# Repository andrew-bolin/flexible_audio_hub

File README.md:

# flexible_audio_hub

## The Challenge

My ears and speakers will last a lifetime (I hope), but home theatre audio standards do not. My old stereo amplifier works fine, why can't I get an HDMI upgrade module that gives it CEC (control via TV remote). If I buy a 5.1 channel amplifier, why do I have to throw it in the bin to upgrade to Atmos?

A modern AVR (Audio-Video Receiver) is a fantastic piece of technology, but they are available only in certain fixed configurations and are not easily modifiable.

## How Will We Alleviate The Problem?

1. A modular "hub" that allows incremental upgrades, e.g. an extra analog input, an extra two channels of amplification, or even another hub...
2. Compatibility with other open source projects in this field.
3. Ability to make use of readily available (cheap!) modules from China.
4. Ability to connect to home automation systems (e.g. limit the volume and turn off the subwoofer if someone's in bed, or play your wake-up alarm at rock concert levels throughout the house)

The modular system will be entirely open-source so that any interested person can make their own module to serve their unique needs (or for fun). Eventually I would like to see compatible modules available from multiple vendors (much like Raspberry Pi & Arduino add-ons).

## (Notes Working Towards) The Specification

[The Current Specification](SPECIFICATION.md) - very much a work in progress!

The first stage will be electrical & communications protocol only.

Currently, I am deciding on a connector - if anyone knows a connector that is a reasonable pitch (0.5 - 2.5mm), keyed, upwards-compatible with extra pins (e.g. a 16-pin plug can fit into a 20-pin socket), and **cheap**, please get in contact!

*Previously, I started a similar project using a backplane, because edge connectors are cheap, but the design I was using had the switching complexity by necessity in every module, was difficult to integrate into a chassis, and did not offer full flexibility for multiple simultaneous outputs. Now I will move that complexity to a "hub" board.*

Each module should (yes, it's optional) have an ID EEPROM & accept a few basic commands (Enable, select channel) via I2C. This can be achieved via a PCA9500 I/O expander or ATtiny, for example. Modules without the ID/Control interface will require more configuration effort and might waste a bit more power (the central hub will probably not have power switches per module).

The hub will be controlled by I2C, and a C++ library will be provided that will be usable via Arduino and Raspberry Pi. The hub will be able to be daisy-chained. 

----

These files are distributed under The TAPR Open Hardware License, version 1.0.  
See LICENSE.txt or https://www.tapr.org/ohl.html

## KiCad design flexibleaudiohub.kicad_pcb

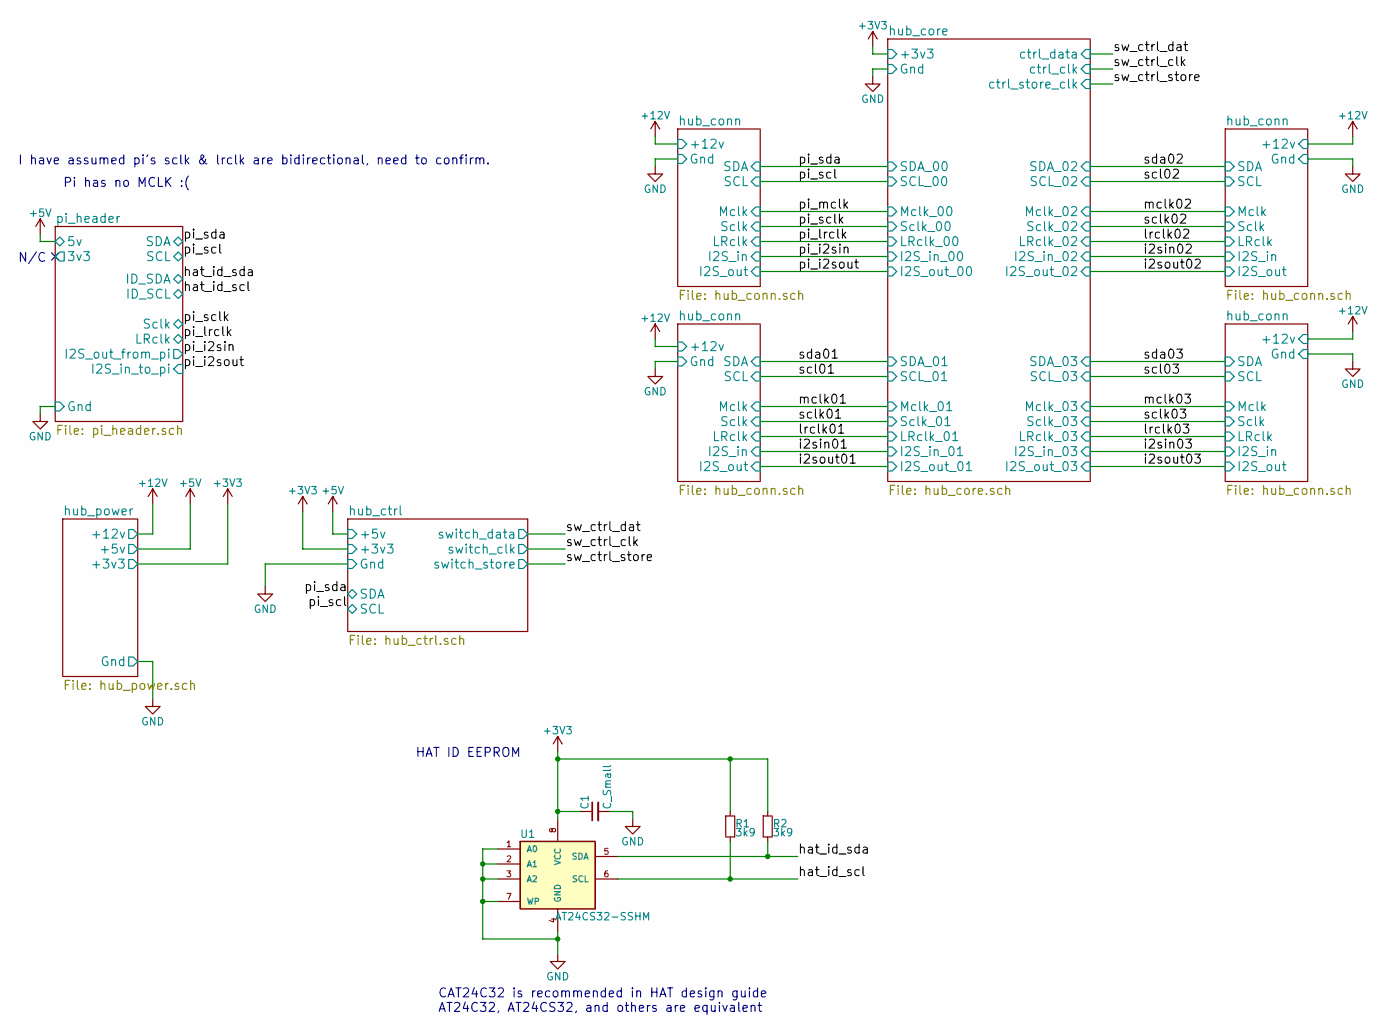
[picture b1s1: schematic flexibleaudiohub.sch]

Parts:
C1: C_Small; C_0805_HandSoldering
R1, R2: 3k9; R_0805_HandSoldering
U1: AT24CS32-SSHM; SOIC-8_3.9x4.9mm_Pitch1.27mm

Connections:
+3V3: C1.1, R1.1, R2.1, U1.8 (VCC); also elsewhere on the board
/hat_id_scl: R1.2, U1.6 (SCL); also elsewhere on the board
/hat_id_sda: R2.2, U1.5 (SDA); also elsewhere on the board
GND: C1.2, U1.1 (A0), U1.2 (A1), U1.3 (A2), U1.4 (GND), U1.7 (WP); also elsewhere on the board

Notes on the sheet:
N/C
Pi has no MCLK :(
I have assumed pi's sclk & lrclk are bidirectional, need to confirm.
HAT ID EEPROM
CAT24C32 is recommended in HAT design guide AT24C32, AT24CS32, and others are equivalent

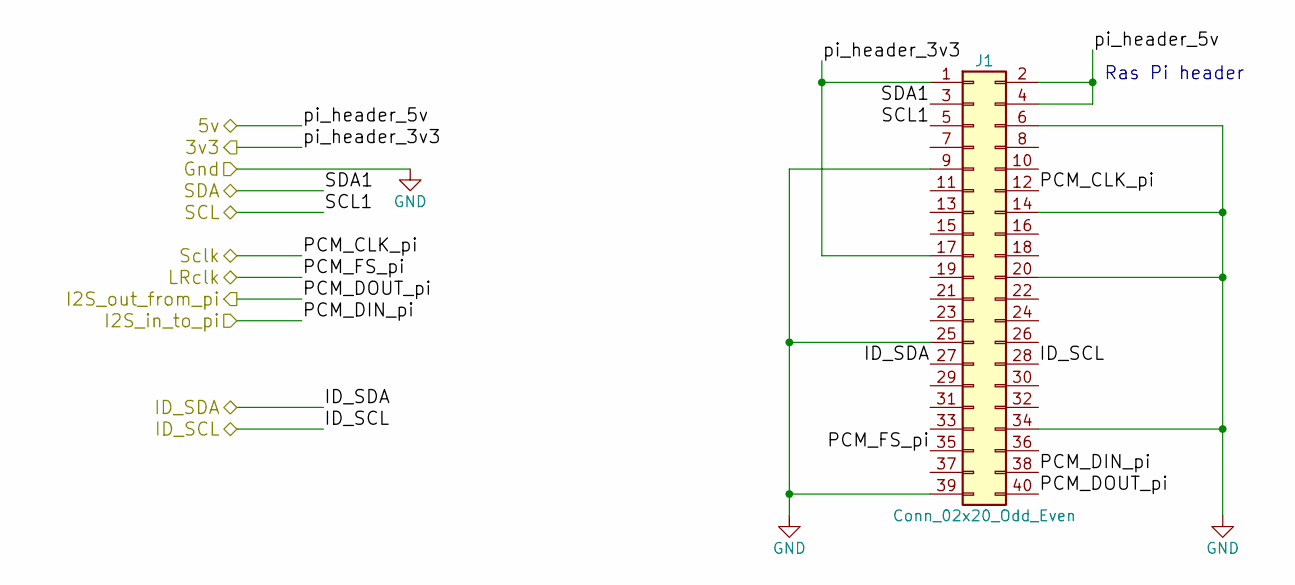
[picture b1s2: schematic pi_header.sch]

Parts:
J1: Conn_02x20_Odd_Even; Pin_Header_Straight_2x20_Pitch2.54mm

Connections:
+5V: J1.2, J1.4; also elsewhere on the board
/hat_id_scl: J1.28; also elsewhere on the board
/hat_id_sda: J1.27; also elsewhere on the board
/pi_header/3v3: J1.1, J1.17
/pi_i2sin: J1.40; also elsewhere on the board
/pi_i2sout: J1.38; also elsewhere on the board
/pi_lrclk: J1.35; also elsewhere on the board
/pi_scl: J1.5; also elsewhere on the board
/pi_sclk: J1.12; also elsewhere on the board
/pi_sda: J1.3; also elsewhere on the board
GND: J1.6, J1.9, J1.14, J1.20, J1.25, J1.34, J1.39; also elsewhere on the board

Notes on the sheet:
Ras Pi header

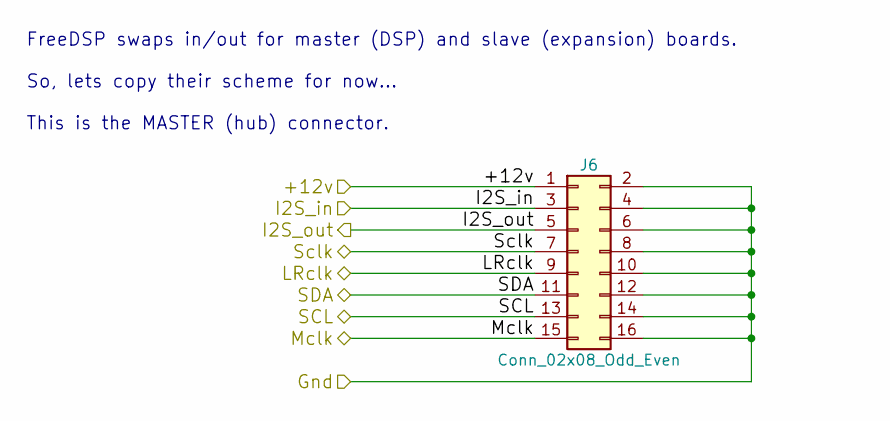
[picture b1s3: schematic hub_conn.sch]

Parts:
J2: Conn_02x08_Odd_Even; Pin_Header_Straight_2x08_Pitch2.54mm

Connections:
+12V: J2.1; also elsewhere on the board
/i2sin03: J2.3; also elsewhere on the board
/i2sout03: J2.5; also elsewhere on the board
/lrclk03: J2.9; also elsewhere on the board
/mclk03: J2.15; also elsewhere on the board
/scl03: J2.13; also elsewhere on the board
/sclk03: J2.7; also elsewhere on the board
/sda03: J2.11; also elsewhere on the board
GND: J2.2, J2.4, J2.6, J2.8, J2.10, J2.12, J2.14, J2.16; also elsewhere on the board

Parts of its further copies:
J4, J5, J6: Conn_02x08_Odd_Even; Pin_Header_Straight_2x08_Pitch2.54mm

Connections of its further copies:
+12V: J4.1, J5.1, J6.1; also elsewhere on the board
/i2sin01: J5.3; also elsewhere on the board
/i2sin02: J4.3; also elsewhere on the board
/i2sout01: J5.5; also elsewhere on the board
/i2sout02: J4.5; also elsewhere on the board
/lrclk01: J5.9; also elsewhere on the board
/lrclk02: J4.9; also elsewhere on the board
/mclk01: J5.15; also elsewhere on the board
/mclk02: J4.15; also elsewhere on the board
/pi_i2sin: J6.3; also elsewhere on the board
/pi_i2sout: J6.5; also elsewhere on the board
/pi_lrclk: J6.9; also elsewhere on the board
/pi_mclk: J6.15; also elsewhere on the board
/pi_scl: J6.13; also elsewhere on the board
/pi_sclk: J6.7; also elsewhere on the board
/pi_sda: J6.11; also elsewhere on the board
/scl01: J5.13; also elsewhere on the board
/scl02: J4.13; also elsewhere on the board
/sclk01: J5.7; also elsewhere on the board
/sclk02: J4.7; also elsewhere on the board
/sda01: J5.11; also elsewhere on the board
/sda02: J4.11; also elsewhere on the board
GND: J4.2, J4.4, J4.6, J4.8, J4.10, J4.12, J4.14, J4.16, J5.2, J5.4, J5.6, J5.8, J5.10, J5.12, J5.14, J5.16, J6.2, J6.4, J6.6, J6.8, J6.10, J6.12, J6.14, J6.16; also elsewhere on the board

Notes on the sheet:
FreeDSP swaps in/out for master (DSP) and slave (expansion) boards. So, lets copy their scheme for now... This is the MASTER (hub) connector.

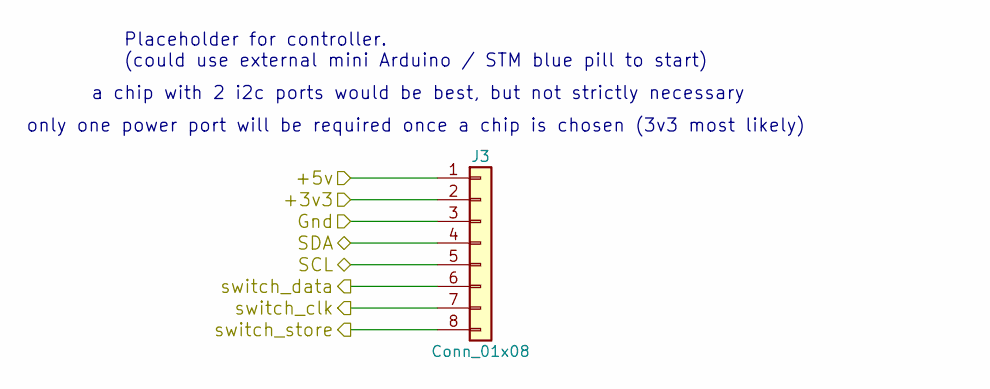
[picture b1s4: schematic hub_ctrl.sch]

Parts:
J3: Conn_01x08; Pin_Header_Straight_1x08_Pitch2.54mm

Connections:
+3V3: J3.2; also elsewhere on the board
+5V: J3.1; also elsewhere on the board
/pi_scl: J3.5; also elsewhere on the board
/pi_sda: J3.4; also elsewhere on the board
/sw_ctrl_clk: J3.7; also elsewhere on the board
/sw_ctrl_dat: J3.6; also elsewhere on the board
/sw_ctrl_store: J3.8; also elsewhere on the board
GND: J3.3; also elsewhere on the board

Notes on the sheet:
Placeholder for controller. (could use external mini Arduino / STM blue pill to start)
a chip with 2 i2c ports would be best, but not strictly necessary
only one power port will be required once a chip is chosen (3v3 most likely)

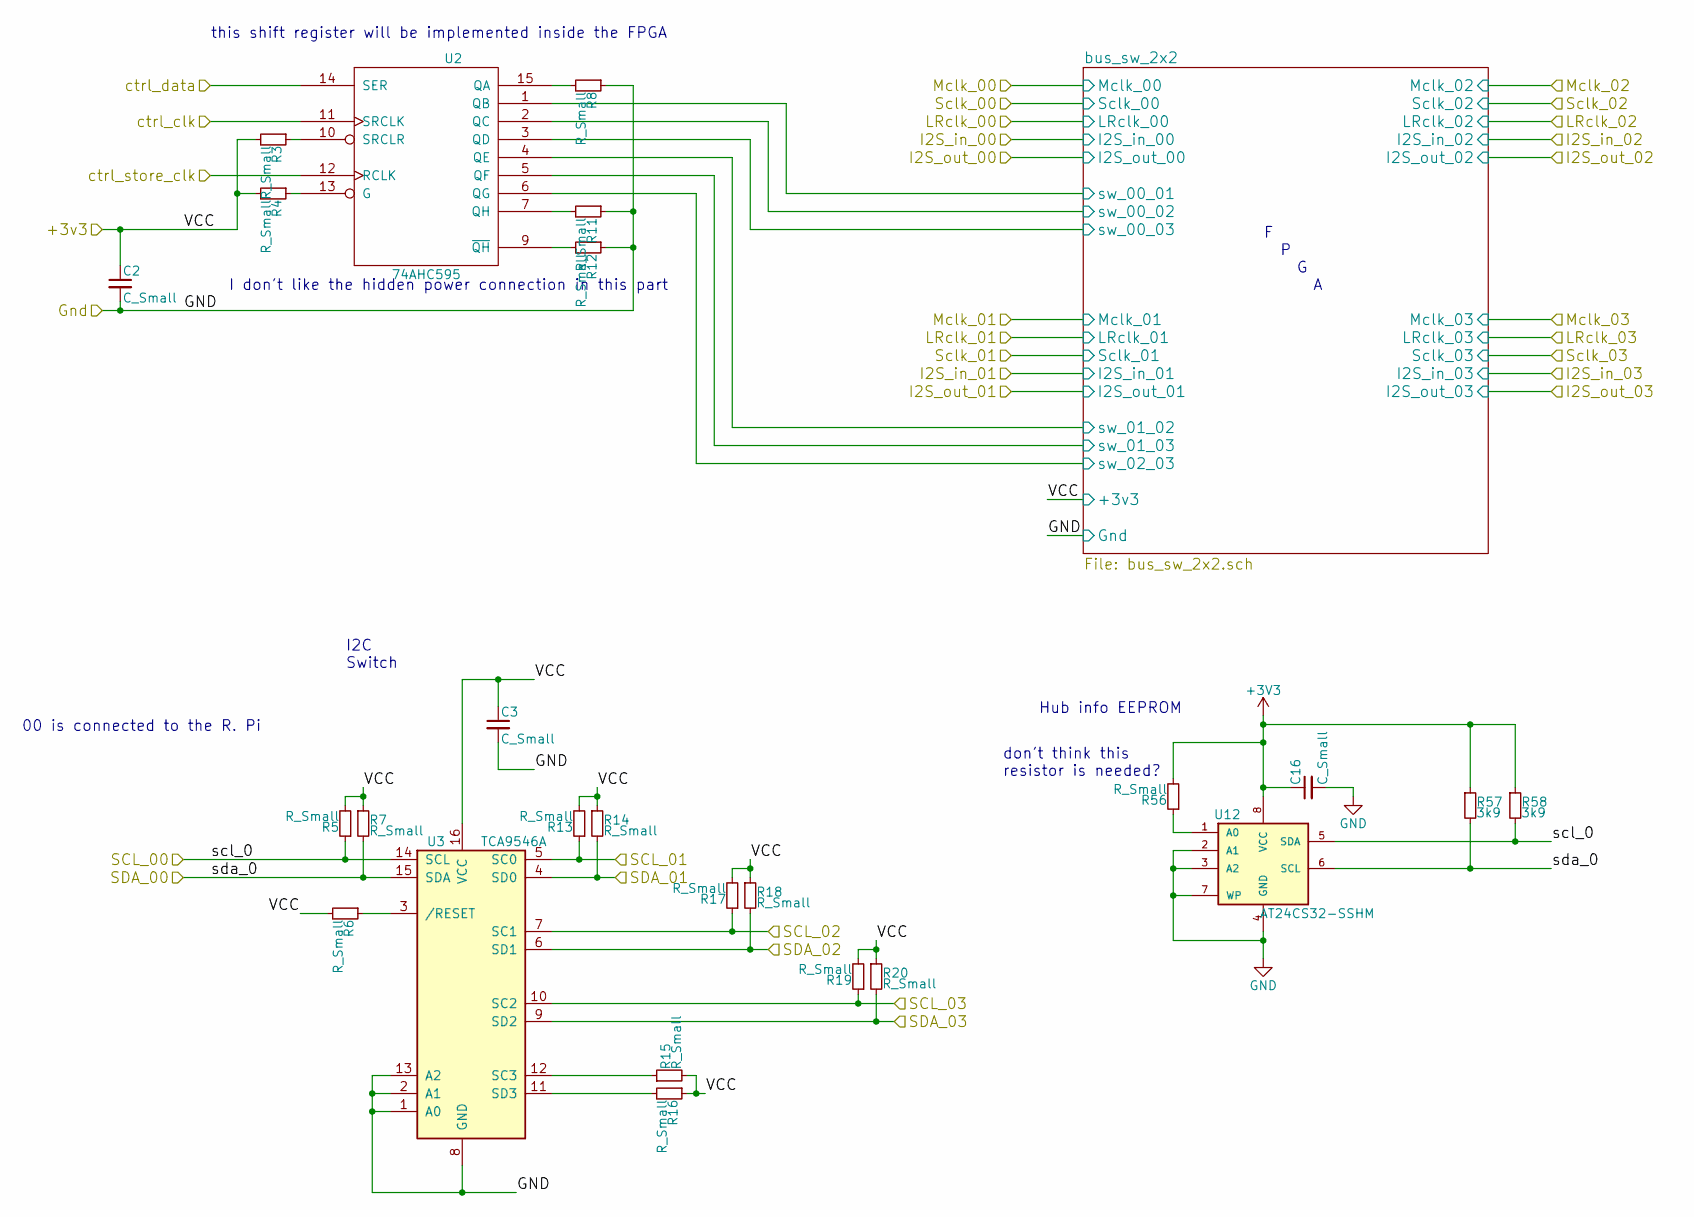
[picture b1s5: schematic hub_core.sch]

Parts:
C2, C3, C16: C_Small; C_0805_HandSoldering
R3, R4, R5, R6, R7, R8, R11, R12, R13, R14, R15, R16, R17, R18, R19, R20, R56: R_Small; R_0805_HandSoldering
R57, R58: 3k9; R_0805_HandSoldering
U2: 74AHC595; SOIC-16_3.9x9.9mm_Pitch1.27mm
U3: TCA9546A; TSSOP-16_4.4x5mm_Pitch0.65mm
U12: AT24CS32-SSHM; SOIC-8_3.9x4.9mm_Pitch1.27mm

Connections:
+3V3: C2.1, C3.1, C16.1, R3.2, R4.2, R5.2, R6.2, R7.1, R13.2, R14.1, R15.2, R16.1, R17.2, R18.1, R19.2, R20.1, R56.2, R57.1, R58.1, U2.16 (VCC), U3.16 (VCC), U12.8 (VCC); also elsewhere on the board
/hub_core/bus_sw_2x2/sw_00_01: U2.1 (QB); also elsewhere on the board
/hub_core/bus_sw_2x2/sw_00_02: U2.2 (QC); also elsewhere on the board
/hub_core/bus_sw_2x2/sw_00_03: U2.3 (QD); also elsewhere on the board
/hub_core/bus_sw_2x2/sw_01_02: U2.4 (QE); also elsewhere on the board
/hub_core/bus_sw_2x2/sw_01_03: U2.5 (QF); also elsewhere on the board
/hub_core/bus_sw_2x2/sw_02_03: U2.6 (QG); also elsewhere on the board
/pi_scl: R5.1, R58.2, U3.14 (SCL), U12.5 (SDA); also elsewhere on the board
/pi_sda: R7.2, R57.2, U3.15 (SDA), U12.6 (SCL); also elsewhere on the board
/scl01: R13.1, U3.5 (SC0); also elsewhere on the board
/scl02: R17.1, U3.7 (SC1); also elsewhere on the board
/scl03: R19.1, U3.10 (SC2); also elsewhere on the board
/sda01: R14.2, U3.4 (SD0); also elsewhere on the board
/sda02: R18.2, U3.6 (SD1); also elsewhere on the board
/sda03: R20.2, U3.9 (SD2); also elsewhere on the board
/sw_ctrl_clk: U2.11 (SRCLK); also elsewhere on the board
/sw_ctrl_dat: U2.14 (SER); also elsewhere on the board
/sw_ctrl_store: U2.12 (RCLK); also elsewhere on the board
GND: C2.2, C3.2, C16.2, R8.1, R11.1, R12.1, U2.8 (GND), U3.1 (A0), U3.2 (A1), U3.8 (GND), U3.13 (A2), U12.2 (A1), U12.3 (A2), U12.4 (GND), U12.7 (WP); also elsewhere on the board
unnamed: R3.1, U2.10 (SRCLR)
unnamed: R4.1, U2.13 (G)
unnamed: R6.1, U3.3 (/RESET)
unnamed: R8.2, U2.15 (QA)
unnamed: R11.2, U2.7 (QH)
unnamed: R12.2, U2.9 (~QH)
unnamed: R15.1, U3.12 (SC3)
unnamed: R16.2, U3.11 (SD3)
unnamed: R56.1, U12.1 (A0)

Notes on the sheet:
I2C Switch
00 is connected to the R. Pi
F P G A
this shift register will be implemented inside the FPGA
I don't like the hidden power connection in this part
Hub info EEPROM
don't think this resistor is needed?

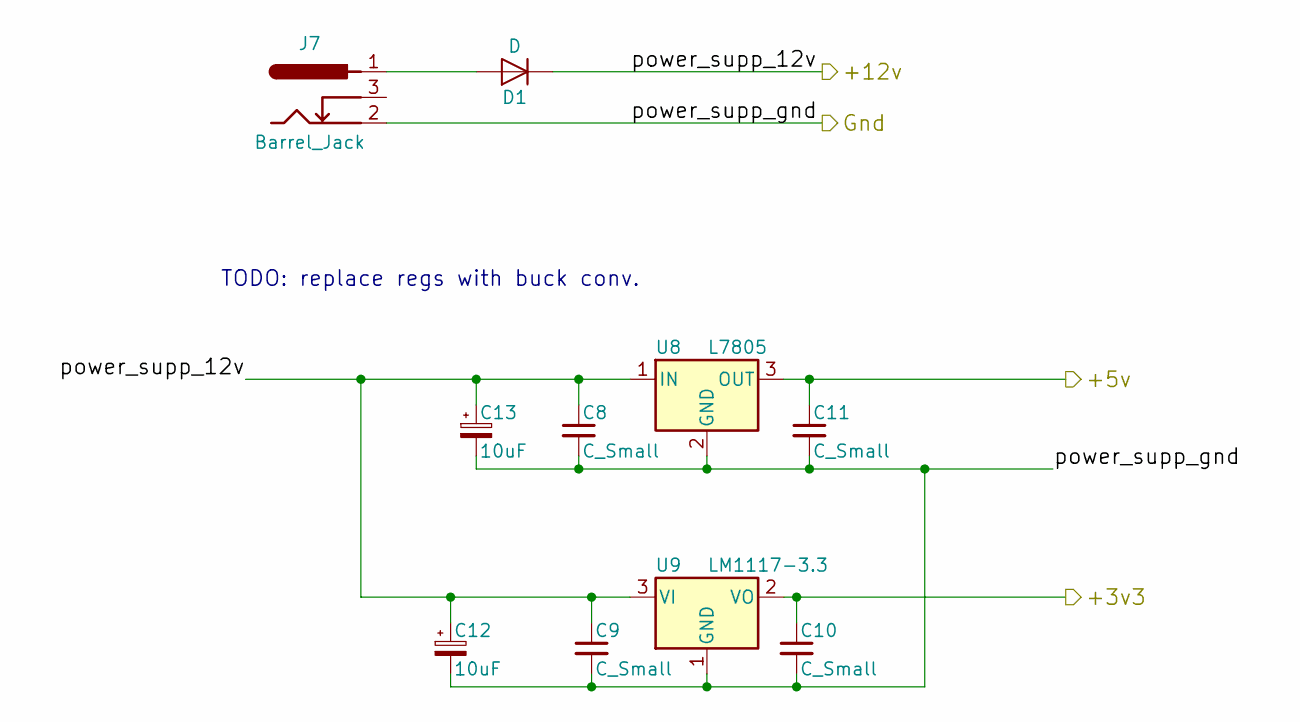
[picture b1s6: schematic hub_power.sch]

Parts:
C8, C9, C10, C11: C_Small; C_0805_HandSoldering
C12, C13: 10uF; CP_Radial_D5.0mm_P2.00mm
D1: D; D_5W_P10.16mm_Horizontal
J7: Barrel_Jack; BARREL_JACK
U8: L7805; TO-220_Vertical
U9: LM1117-3.3; TO-220_Vertical

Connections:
+3V3: C10.1, U9.2 (VO); also elsewhere on the board
+5V: C11.1, U8.3 (OUT); also elsewhere on the board
+12V: C8.1, C9.1, C12.1, C13.1, D1.1 (K), U8.1 (IN), U9.3 (VI); also elsewhere on the board
GND: C8.2, C9.2, C10.2, C11.2, C12.2, C13.2, J7.2, U8.2 (GND), U9.1 (GND); also elsewhere on the board
unnamed: D1.2 (A), J7.1

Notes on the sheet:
TODO: replace regs with buck conv.

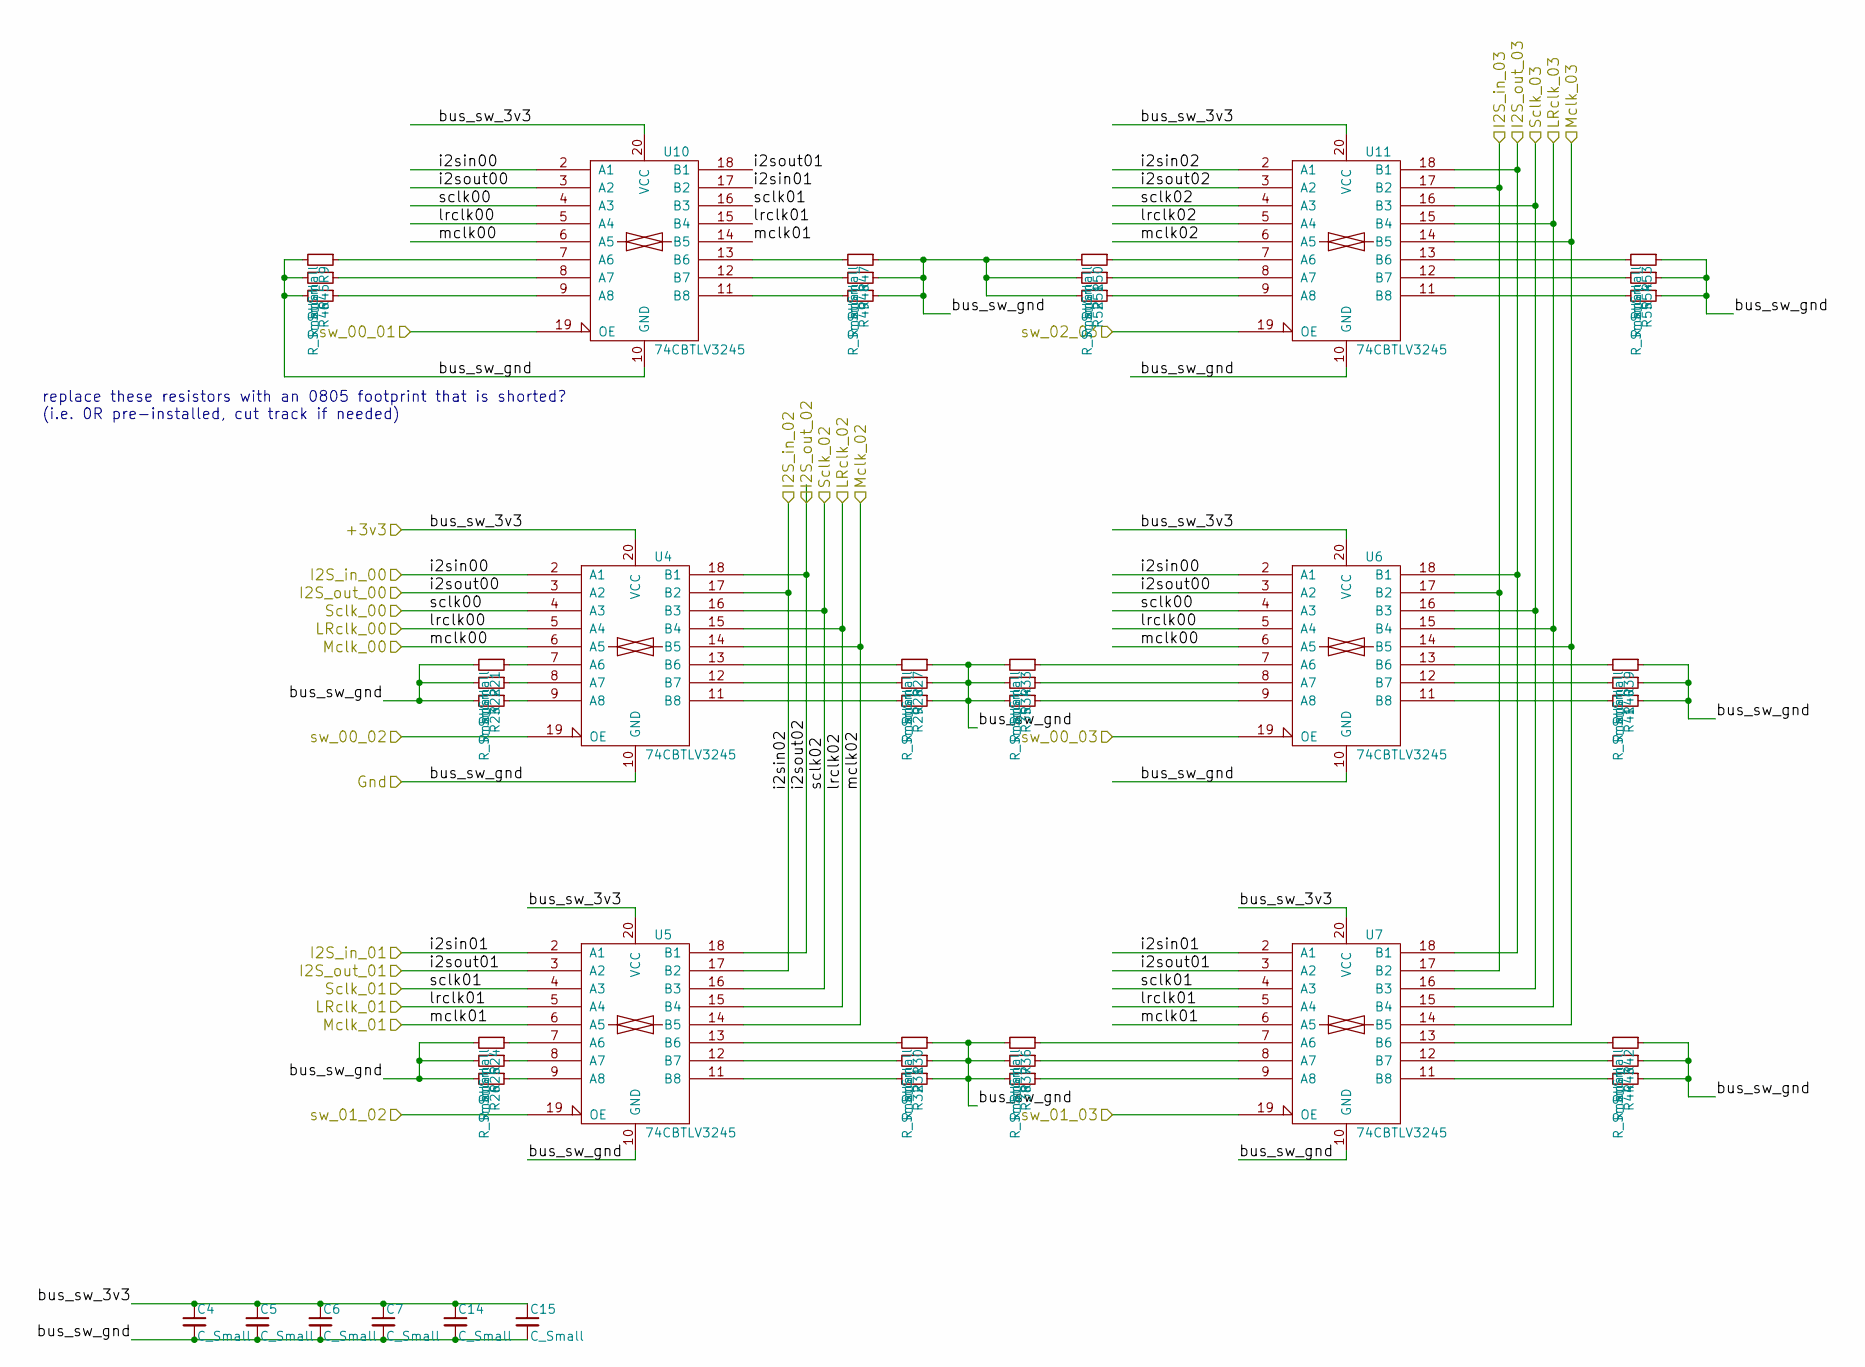
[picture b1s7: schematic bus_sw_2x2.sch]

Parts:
C4, C5, C6, C7, C14, C15: C_Small; C_0805_HandSoldering
R9, R21, R22, R23, R24, R25, R26, R27, R28, R29, R30, R31, R32, R33, R34, R35, R36, R37, R38, R39, R40, R41, R42, R43, R44, R45, R46, R47, R48, R49, R50, R51, R52, R53, R54, R55: R_Small; R_0805_HandSoldering
U4, U5, U6, U7, U10, U11: 74CBTLV3245; TSSOP-20_4.4x6.5mm_Pitch0.65mm

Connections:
+3V3: C4.1, C5.1, C6.1, C7.1, C14.1, C15.1, U4.20 (VCC), U5.20 (VCC), U6.20 (VCC), U7.20 (VCC), U10.20 (VCC), U11.20 (VCC); also elsewhere on the board
/hub_core/bus_sw_2x2/sw_00_01: U10.19 (OE); also elsewhere on the board
/hub_core/bus_sw_2x2/sw_00_02: U4.19 (OE); also elsewhere on the board
/hub_core/bus_sw_2x2/sw_00_03: U6.19 (OE); also elsewhere on the board
/hub_core/bus_sw_2x2/sw_01_02: U5.19 (OE); also elsewhere on the board
/hub_core/bus_sw_2x2/sw_01_03: U7.19 (OE); also elsewhere on the board
/hub_core/bus_sw_2x2/sw_02_03: U11.19 (OE); also elsewhere on the board
/i2sin01: U5.2 (A1), U7.2 (A1), U10.17 (B2); also elsewhere on the board
/i2sin02: U4.17 (B2), U5.17 (B2), U11.2 (A1); also elsewhere on the board
/i2sin03: U6.17 (B2), U7.17 (B2), U11.17 (B2); also elsewhere on the board
/i2sout01: U5.3 (A2), U7.3 (A2), U10.18 (B1); also elsewhere on the board
/i2sout02: U4.18 (B1), U5.18 (B1), U11.3 (A2); also elsewhere on the board
/i2sout03: U6.18 (B1), U7.18 (B1), U11.18 (B1); also elsewhere on the board
/lrclk01: U5.5 (A4), U7.5 (A4), U10.15 (B4); also elsewhere on the board
/lrclk02: U4.15 (B4), U5.15 (B4), U11.5 (A4); also elsewhere on the board
/lrclk03: U6.15 (B4), U7.15 (B4), U11.15 (B4); also elsewhere on the board
/mclk01: U5.6 (A5), U7.6 (A5), U10.14 (B5); also elsewhere on the board
/mclk02: U4.14 (B5), U5.14 (B5), U11.6 (A5); also elsewhere on the board
/mclk03: U6.14 (B5), U7.14 (B5), U11.14 (B5); also elsewhere on the board
/pi_i2sin: U4.2 (A1), U6.2 (A1), U10.2 (A1); also elsewhere on the board
/pi_i2sout: U4.3 (A2), U6.3 (A2), U10.3 (A2); also elsewhere on the board
/pi_lrclk: U4.5 (A4), U6.5 (A4), U10.5 (A4); also elsewhere on the board
/pi_mclk: U4.6 (A5), U6.6 (A5), U10.6 (A5); also elsewhere on the board
/pi_sclk: U4.4 (A3), U6.4 (A3), U10.4 (A3); also elsewhere on the board
/sclk01: U5.4 (A3), U7.4 (A3), U10.16 (B3); also elsewhere on the board
/sclk02: U4.16 (B3), U5.16 (B3), U11.4 (A3); also elsewhere on the board
/sclk03: U6.16 (B3), U7.16 (B3), U11.16 (B3); also elsewhere on the board
GND: C4.2, C5.2, C6.2, C7.2, C14.2, C15.2, R9.2, R21.2, R22.2, R23.2, R24.2, R25.2, R26.2, R27.1, R28.1, R29.1, R30.1, R31.1, R32.1, R33.2, R34.2, R35.2, R36.2, R37.2, R38.2, R39.1, R40.1, R41.1, R42.1, R43.1, R44.1, R45.2, R46.2, R47.1, R48.1, R49.1, R50.2, R51.2, R52.2, R53.1, R54.1, R55.1, U4.10 (GND), U5.10 (GND), U6.10 (GND), U7.10 (GND), U10.10 (GND), U11.10 (GND); also elsewhere on the board
unnamed: R9.1, U10.7 (A6)
unnamed: R21.1, U4.7 (A6)
unnamed: R22.1, U4.8 (A7)
unnamed: R23.1, U4.9 (A8)
unnamed: R24.1, U5.7 (A6)
unnamed: R25.1, U5.8 (A7)
unnamed: R26.1, U5.9 (A8)
unnamed: R27.2, U4.13 (B6)
unnamed: R28.2, U4.12 (B7)
unnamed: R29.2, U4.11 (B8)
unnamed: R30.2, U5.13 (B6)
unnamed: R31.2, U5.12 (B7)
unnamed: R32.2, U5.11 (B8)
unnamed: R33.1, U6.7 (A6)
unnamed: R34.1, U6.8 (A7)
unnamed: R35.1, U6.9 (A8)
unnamed: R36.1, U7.7 (A6)
unnamed: R37.1, U7.8 (A7)
unnamed: R38.1, U7.9 (A8)
unnamed: R39.2, U6.13 (B6)
unnamed: R40.2, U6.12 (B7)
unnamed: R41.2, U6.11 (B8)
unnamed: R42.2, U7.13 (B6)
unnamed: R43.2, U7.12 (B7)
unnamed: R44.2, U7.11 (B8)
unnamed: R45.1, U10.8 (A7)
unnamed: R46.1, U10.9 (A8)
unnamed: R47.2, U10.13 (B6)
unnamed: R48.2, U10.12 (B7)
unnamed: R49.2, U10.11 (B8)
unnamed: R50.1, U11.7 (A6)
unnamed: R51.1, U11.8 (A7)
unnamed: R52.1, U11.9 (A8)
unnamed: R53.2, U11.13 (B6)
unnamed: R54.2, U11.12 (B7)
unnamed: R55.2, U11.11 (B8)

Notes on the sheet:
replace these resistors with an 0805 footprint that is shorted? (i.e. 0R pre-installed, cut track if needed)

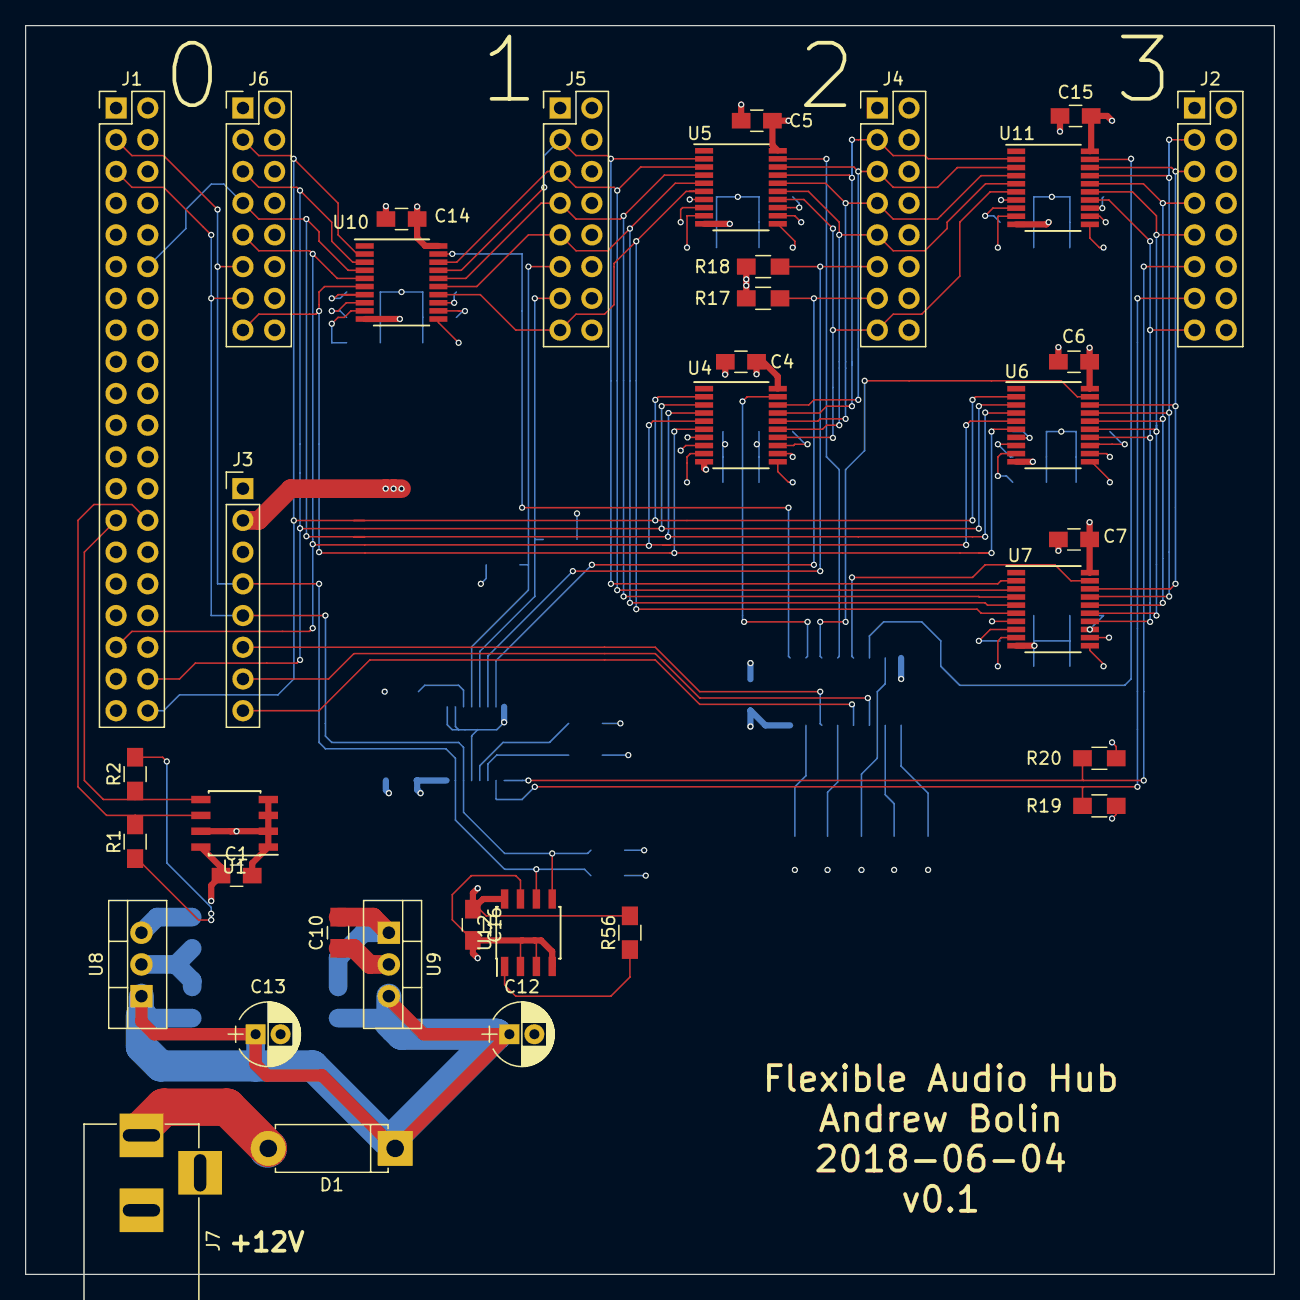
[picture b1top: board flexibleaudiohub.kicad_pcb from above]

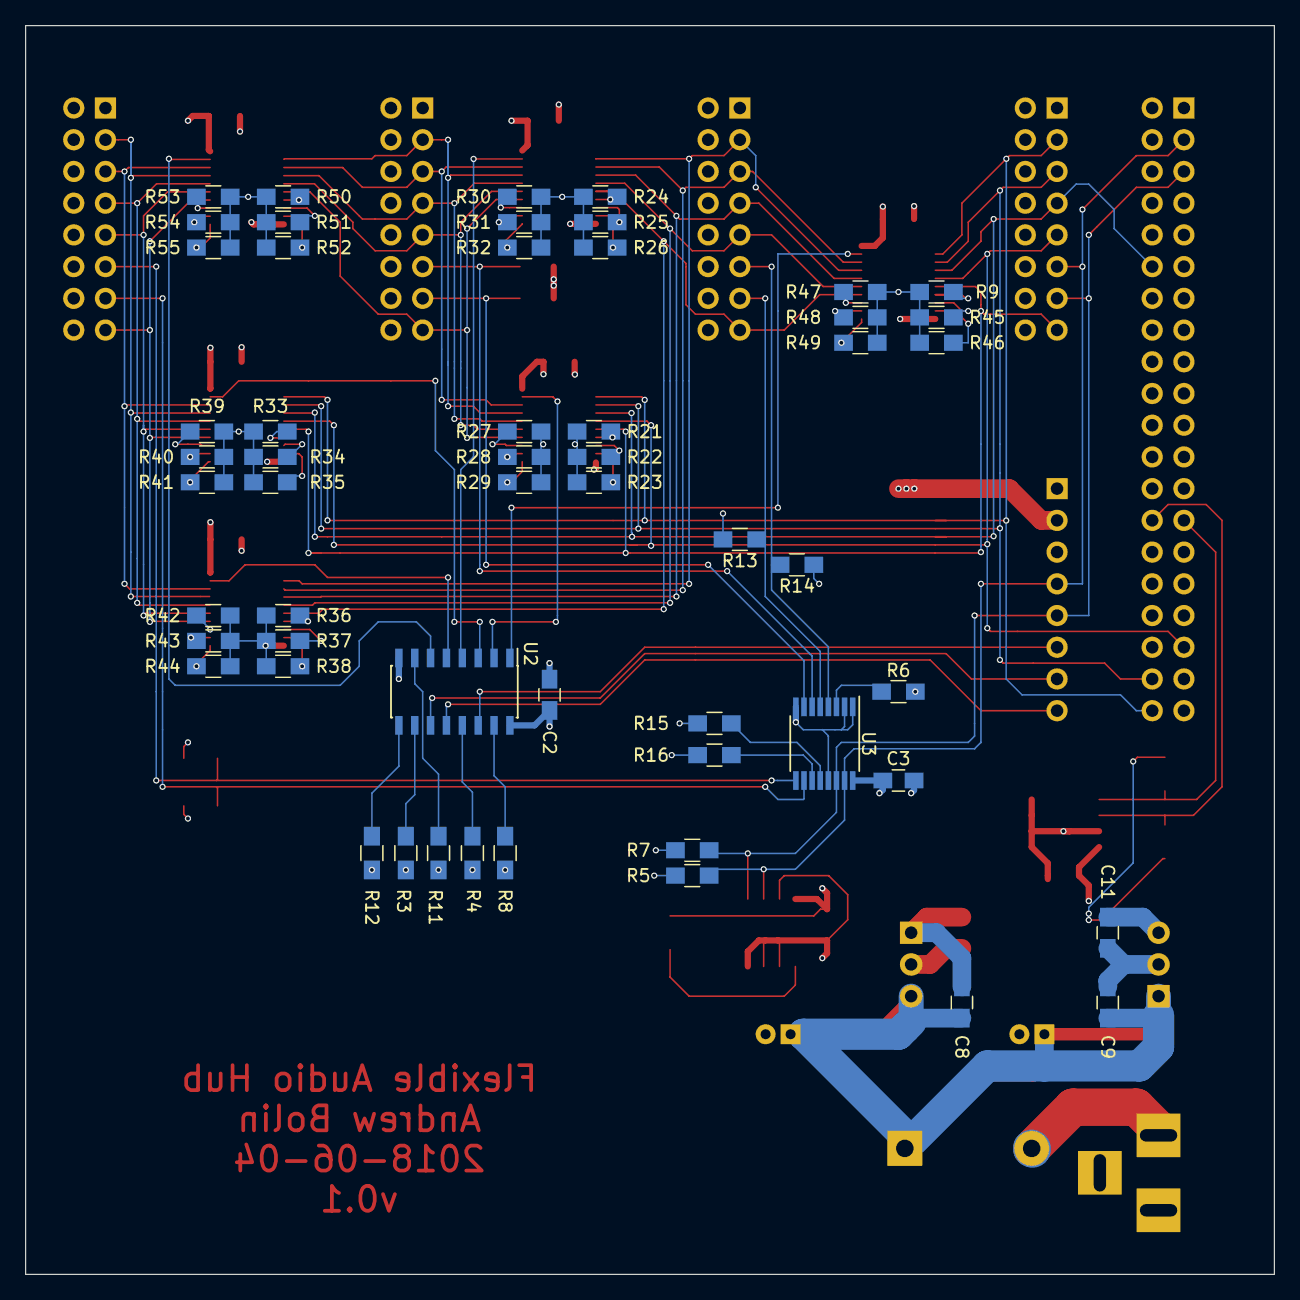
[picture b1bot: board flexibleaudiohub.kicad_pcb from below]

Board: 4 copper layers, 100.0 x 100.0 mm, 91 parts (55 on the bottom side), 90 nets.

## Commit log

2018-04-19 pcb skeleton (in progress)
2018-04-19 license
    The TAPR Open Hardware License v1.0
2018-04-22 preliminary schematic using discrete logic chips
2018-04-22 test spec md
2018-04-22 preliminary specification
2018-04-22 fix link
2018-04-22 ACTUALLY fix link
2018-04-22 PDF schematic
2018-06-08 finished layout
